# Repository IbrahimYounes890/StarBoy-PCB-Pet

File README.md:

# LEAFIE

This is my Starbie-inspired PCB pet project --> LEAFIE!

LEAFIE is a tiny motion-controlled digital pet, created using Starbie's guide on GitHub. He is also a pet that is controlled by motion rather than using controls.

## What is it?

It is a pet that sits on your desk, displays personality and character on the display, and can be interacted with via two buttons and a motion sensor. 
It includes a microcontroller, display, motion sensor, and environmental sensor in a custom-designed PCB in the shape of a Canadian maple leaf.

## How was it made?

I used the beginner [Starbie project](https://halflife.hackclub.com/) for the exact components and firmware. But I took creative liberties when designing the board itself. I decided to use a maple leaf, and I had to change up a few of the connections to make my PCB flow better.

## Why was it designed this way?

I chose the PCB design to look like a maple leaf, and added Canadian-themed symbols all over the back and front to show my love for my country Canada. I am a proud Canadian and thought this was a very cool idea to showcase my spirit!

## Project status

Currently, PCB files are complete, and firmware is ready, waiting for the project to be approved and shipped in week 6 of half-life!

## Bill of Materials (BOM)

| Part | What it's for | Qty | Unit | Total | Vendor | Link |
| :--- | :--- | :---: | :---: | :---: | :--- | :--- |
| **DHT11 Digital Temp & Humidity Sensor Module** | Environmental Sensor For Pet | 1 | $2.31 | $2.31 | AliExpress | [View Link](https://www.aliexpress.com/item/1005008818897051.html?spm=a2g0o.cart.0.0.71f338dapXPrZD&mp=1&pdp_npi=6%40dis%21USD%21USD+2.32%21USD+2.18%21%21USD+2.18%21%21%21%402101e75417935899983408413e1096%2112000046802736832%21ct%21CA%218284808141%21%211%210%21) |
| **ESP 32 - C3 Mini** | For controlling the brain | 1 | $5.52 | $5.52 | AliExpress | [View Link](https://www.aliexpress.com/item/1005007239162635.html?spm=a2g0o.cart.0.0.71f338dapXPrZD&mp=1&pdp_npi=6%40dis%21USD%21USD+18.52%21USD+4.58%21%21USD+4.58%21%21%21%402101e75417935899983408413e1096%2112000039916348342%21ct%21CA%218284808141%21%211%210%21&pdp_ext_f=%7B%22cart2PdpParams%22%3A%7B%22pdpBusinessMode%22%3A%22retail%22%7D%7D) |
| **Resistors (comes with mutliple values)** | Resistors for project | 300 | ? | $1.19 | AliExpress |[View Link](https://www.aliexpress.com/item/1005011772534173.html?spm=a2g0o.cart.0.0.71f338dapXPrZD&mp=1&pdp_npi=6%40dis%21USD%21USD+4.20%21USD+1.19%21%21USD+1.19%21%21%21%402101e75417935899983408413e1096%2112000056500803485%21ct%21CA%218284808141%21%211%210%21)|
| **Switches** | For switches input to pet | 10 | ? | $1.19 | AliExpress | [View Link](https://www.aliexpress.com/item/1005008089864080.html?spm=a2g0o.cart.0.0.71f338dapXPrZD&mp=1&pdp_npi=6%40dis%21USD%21USD+4.13%21USD+4.13%21%21USD+4.13%21%21%21%402101e75417935899983408413e1096%2112000045838677521%21ct%21CA%218284808141%21%211%210%21) |
| **MPU6050 Module 6 Axis IMU** | For the motion control | 1 | $2.78 | $1.66 | AliExpress | [View Link](https://www.aliexpress.com/item/1005012722676424.html?spm=a2g0o.cart.0.0.3fcc38da5d1nRa&mp=1&pdp_npi=6%40dis%21USD%21USD+3.57%21USD+2.78%21%21USD+2.78%21%21%21%4021032e4e17935918278648994e0ece%2112000059167286842%21ct%21CA%218284808141%21%211%210%21) |
| **LEAFIE PCB** | PCB for project | 1 | free with coupon| $0 | JLCPCB | [View Link](https://jlcpcb.com) |
| **0.96 OLED** | Visual output | 1 | $4.16 | $4.16 | AliExpress | [View Link](http://aliexpress.com/item/1005006141235306.html?spm=a2g0o.cart.0.0.710b38daroD91k&mp=1&pdp_npi=6%40dis%21USD%21USD+4.16%21USD+4.16%21%21USD+4.16%21%21%21%4021030cd817935910208061059e0f72%2112000037894450874%21ct%21CA%218284808141%21%211%210%21)|

* **Parts Subtotal:** $19.02
* **Tax & Shipping:** $4.39
* **Total Estimated Cost:** **$23.41**

## Repository contents

- `PCB/` - KiCad source files and fabrication exports
- `Firmware/` - Arduino IDE starter sketch

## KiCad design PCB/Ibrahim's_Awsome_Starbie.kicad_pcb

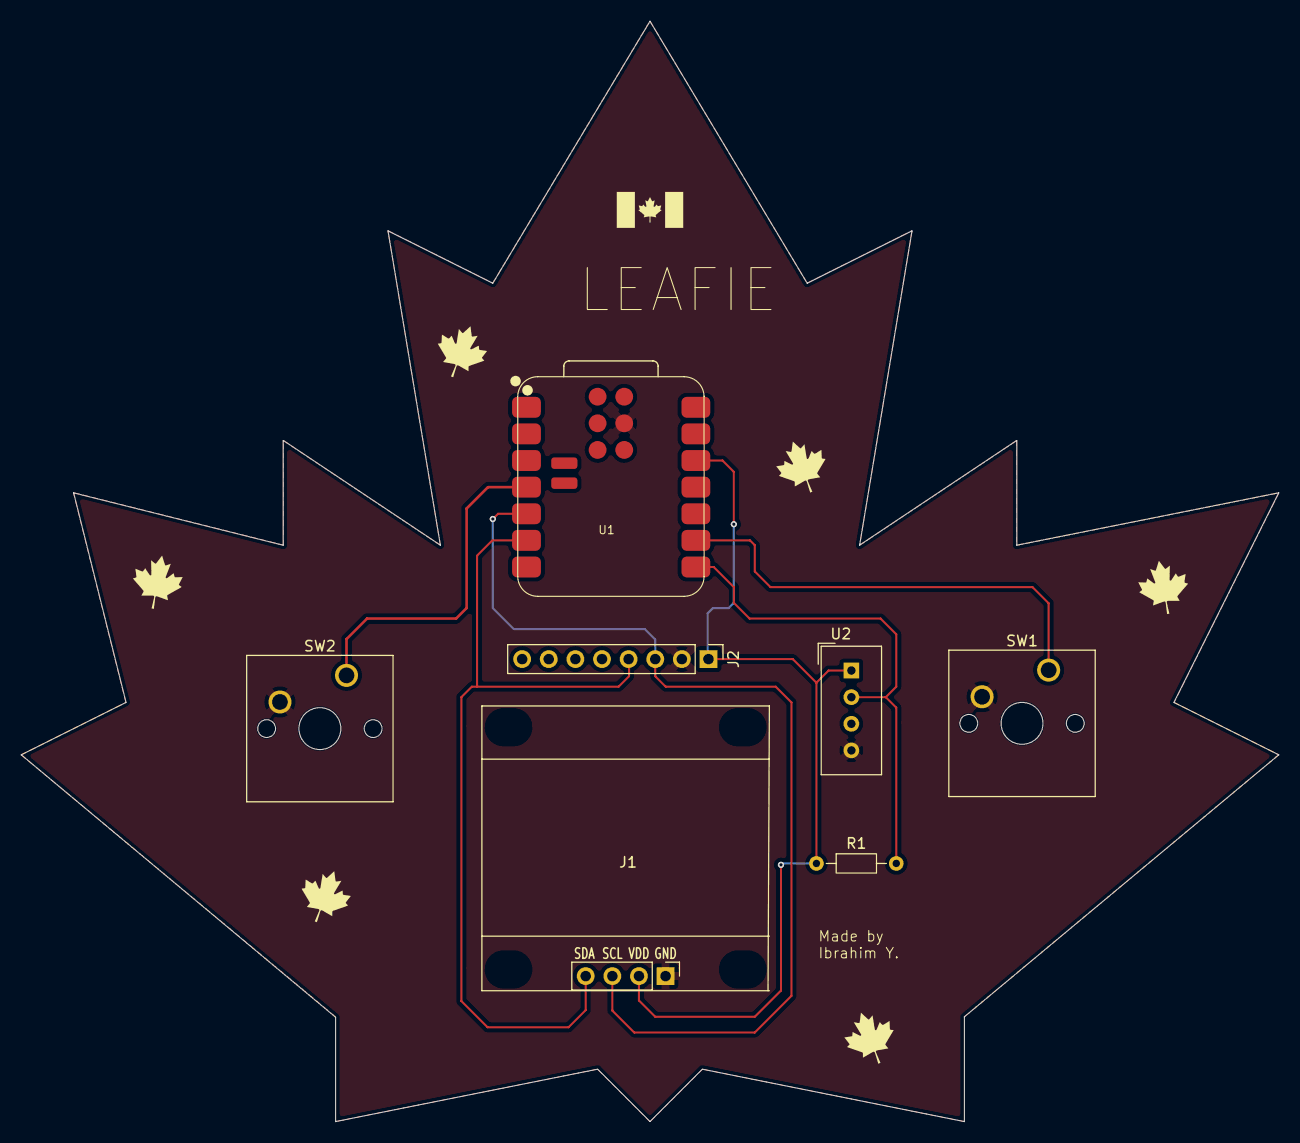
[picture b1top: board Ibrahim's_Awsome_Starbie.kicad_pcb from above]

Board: 2 copper layers, 120.0 x 105.0 mm, 7 parts (0 on the bottom side), 7 nets.

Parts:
J1: Conn_01x04_Pin; Display_128x64_096_I2C
J2: Conn_01x08_Pin; PinHeader_1x08_P2.54mm_Vertical
R1: 10k; R_Axial_DIN0204_L3.6mm_D1.6mm_P7.62mm_Horizontal
SW1, SW2: SW_Push; SW_Cherry_MX_1.00u_PCB
U1: XIAO-ESP32-C3-SMD
U2: DHT11; Aosong_DHT11_5.5x12.0_P2.54mm

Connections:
+3.3V: J1.2, J2.1, R1.1, U1.12 (3V3_OUT), U2.1 (VDD)
/DHT11 DATA: R1.2, U1.8 (D7), U2.2 (DATA)
/GPIO2: SW1.1, U1.9 (D8)
/GPIO3: SW2.1, U1.4 (D3)
/SCL: J1.3, J2.3, U1.5 (D4)
/SDA: J1.4, J2.4, U1.6 (D5)
GND: J1.1, J2.2, SW1.2, SW2.2, U1.13 (GND), U1.18 (GND), U2.4 (GND)
